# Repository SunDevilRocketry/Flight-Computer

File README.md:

<h1>Flight Computer</h1>

<p><b>Current PCB Revision:</b> 2.0</p>
<p><b>PCB Part Number:</b> A0002</p>

<p>The Avionics team aims to produce a general purpose flight computer 
 for use in high powered rocketry projects that require an embedded processor
specialized for state estimation and control system implementation. The Avionics
flight computer PCB uses an ARM Microcontroller with embedded control and 
navigation sensors to provide a computationally capable embedded protoyping 
platform for high powered rocketry projects with minimal wiring and a small
 form factor.</p>

<b>Working Directory Structure:</b>
 
 <p>
doc: documentation
    
src: source design files, e.g. schematic and board files
 
lib: libraries for schematic symbols and footprints
 
production: files needed for pcb fabrication, e.g. gerbers, profile, drill fi    le
 
 sim: simulation files 
  
 cad: 3d models
   
 img: images of circuit/footprints for github display 
 </p>

<h2>3D Model: </h2>

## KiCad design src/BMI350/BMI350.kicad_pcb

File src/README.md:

<h1>Source Design Files</h1>

Folder for all PCB design files, including project, schematic, and PCB layout 
files

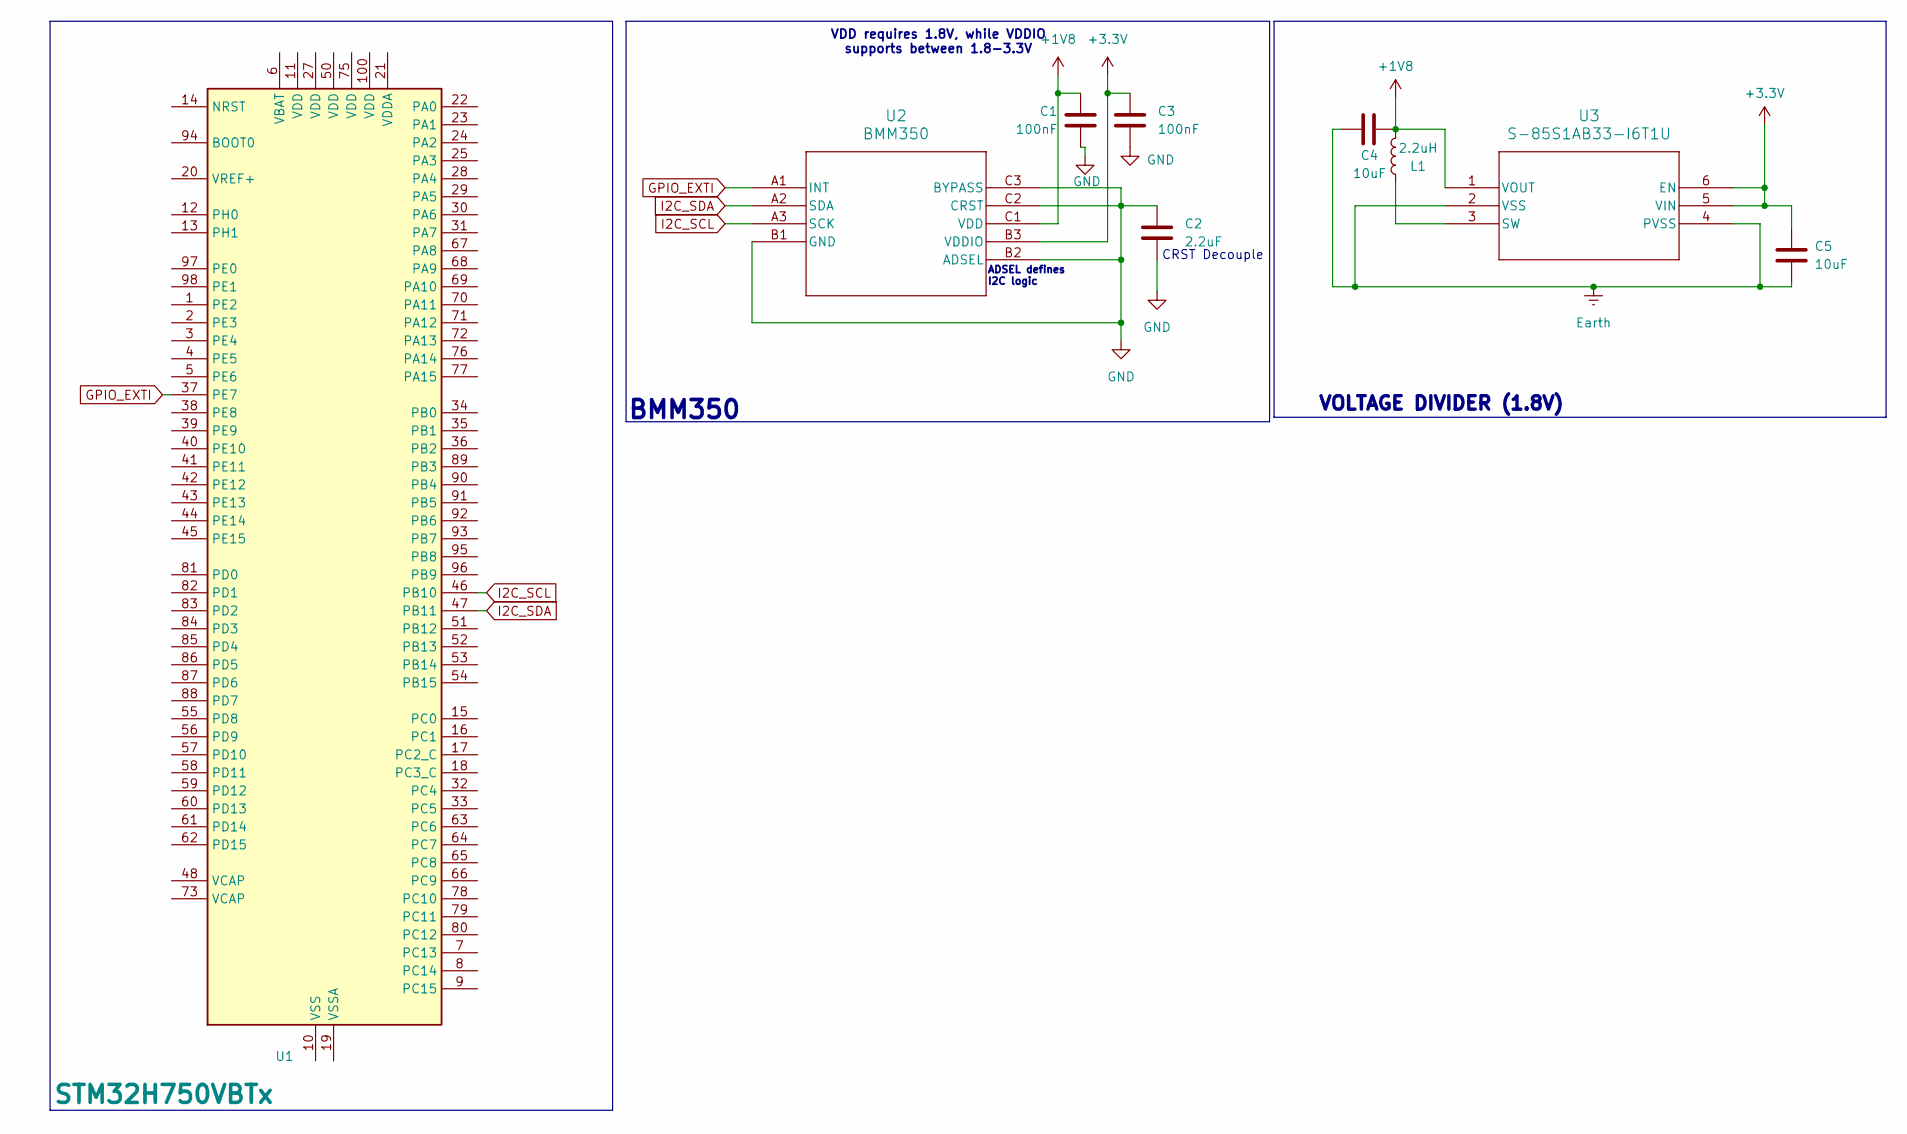
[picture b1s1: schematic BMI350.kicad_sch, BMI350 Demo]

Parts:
C1, C3: 100nF; C_0201_0603Metric
C2: 2.2uF; C_0201_0603Metric
C4, C5: 10uF; C_0201_0603Metric
L1: 2.2uH; L_0201_0603Metric
U1: STM32H750VBTx; LQFP-100_14x14mm_P0.5mm
U2: BMM350; BGA9_BMM350_BOS
U3: S-85S1AB33-I6T1U; SNT-6A-A-PKG_PG006-A-P-SD-2.1_ABL

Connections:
+1V8: C1.2, C4.2, L1.2, U2.C1 (VDD), U3.1 (VOUT)
+3.3V: C3.1, C5.1, U2.B3 (VDDIO), U3.5 (VIN), U3.6 (EN)
Earth: C4.1, C5.2, U3.2 (VSS), U3.4 (PVSS)
GND: C1.1, C2.1, C2.2, C3.2, U2.B1 (GND), U2.B2 (ADSEL), U2.C2 (CRST), U2.C3 (BYPASS)
GPIO_EXTI: U1.37 (PE7), U2.A1 (INT)
I2C_SCL: U1.46 (PB10), U2.A3 (SCK)
I2C_SDA: U1.47 (PB11), U2.A2 (SDA)
unnamed: U1.10 (VSS), U1.26 (VSS), U1.49 (VSS), U1.74 (VSS), U1.99 (VSS)
unnamed: L1.1, U3.3 (SW)

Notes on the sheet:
VOLTAGE DIVIDER (1.8V)
CRST Decouple
BMM350
VDD requires 1.8V, while VDDIO supports between 1.8-3.3V
ADSEL defines I2C logic

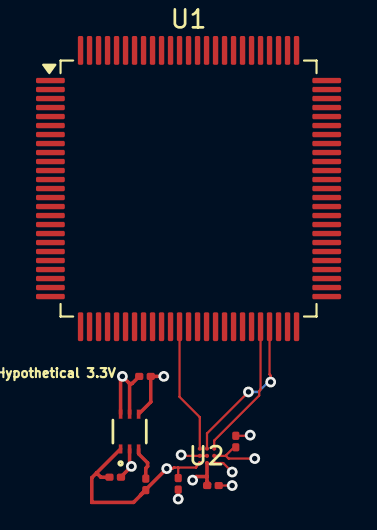
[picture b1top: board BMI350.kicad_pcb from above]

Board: 2 copper layers, 9 parts (0 on the bottom side), 9 nets.

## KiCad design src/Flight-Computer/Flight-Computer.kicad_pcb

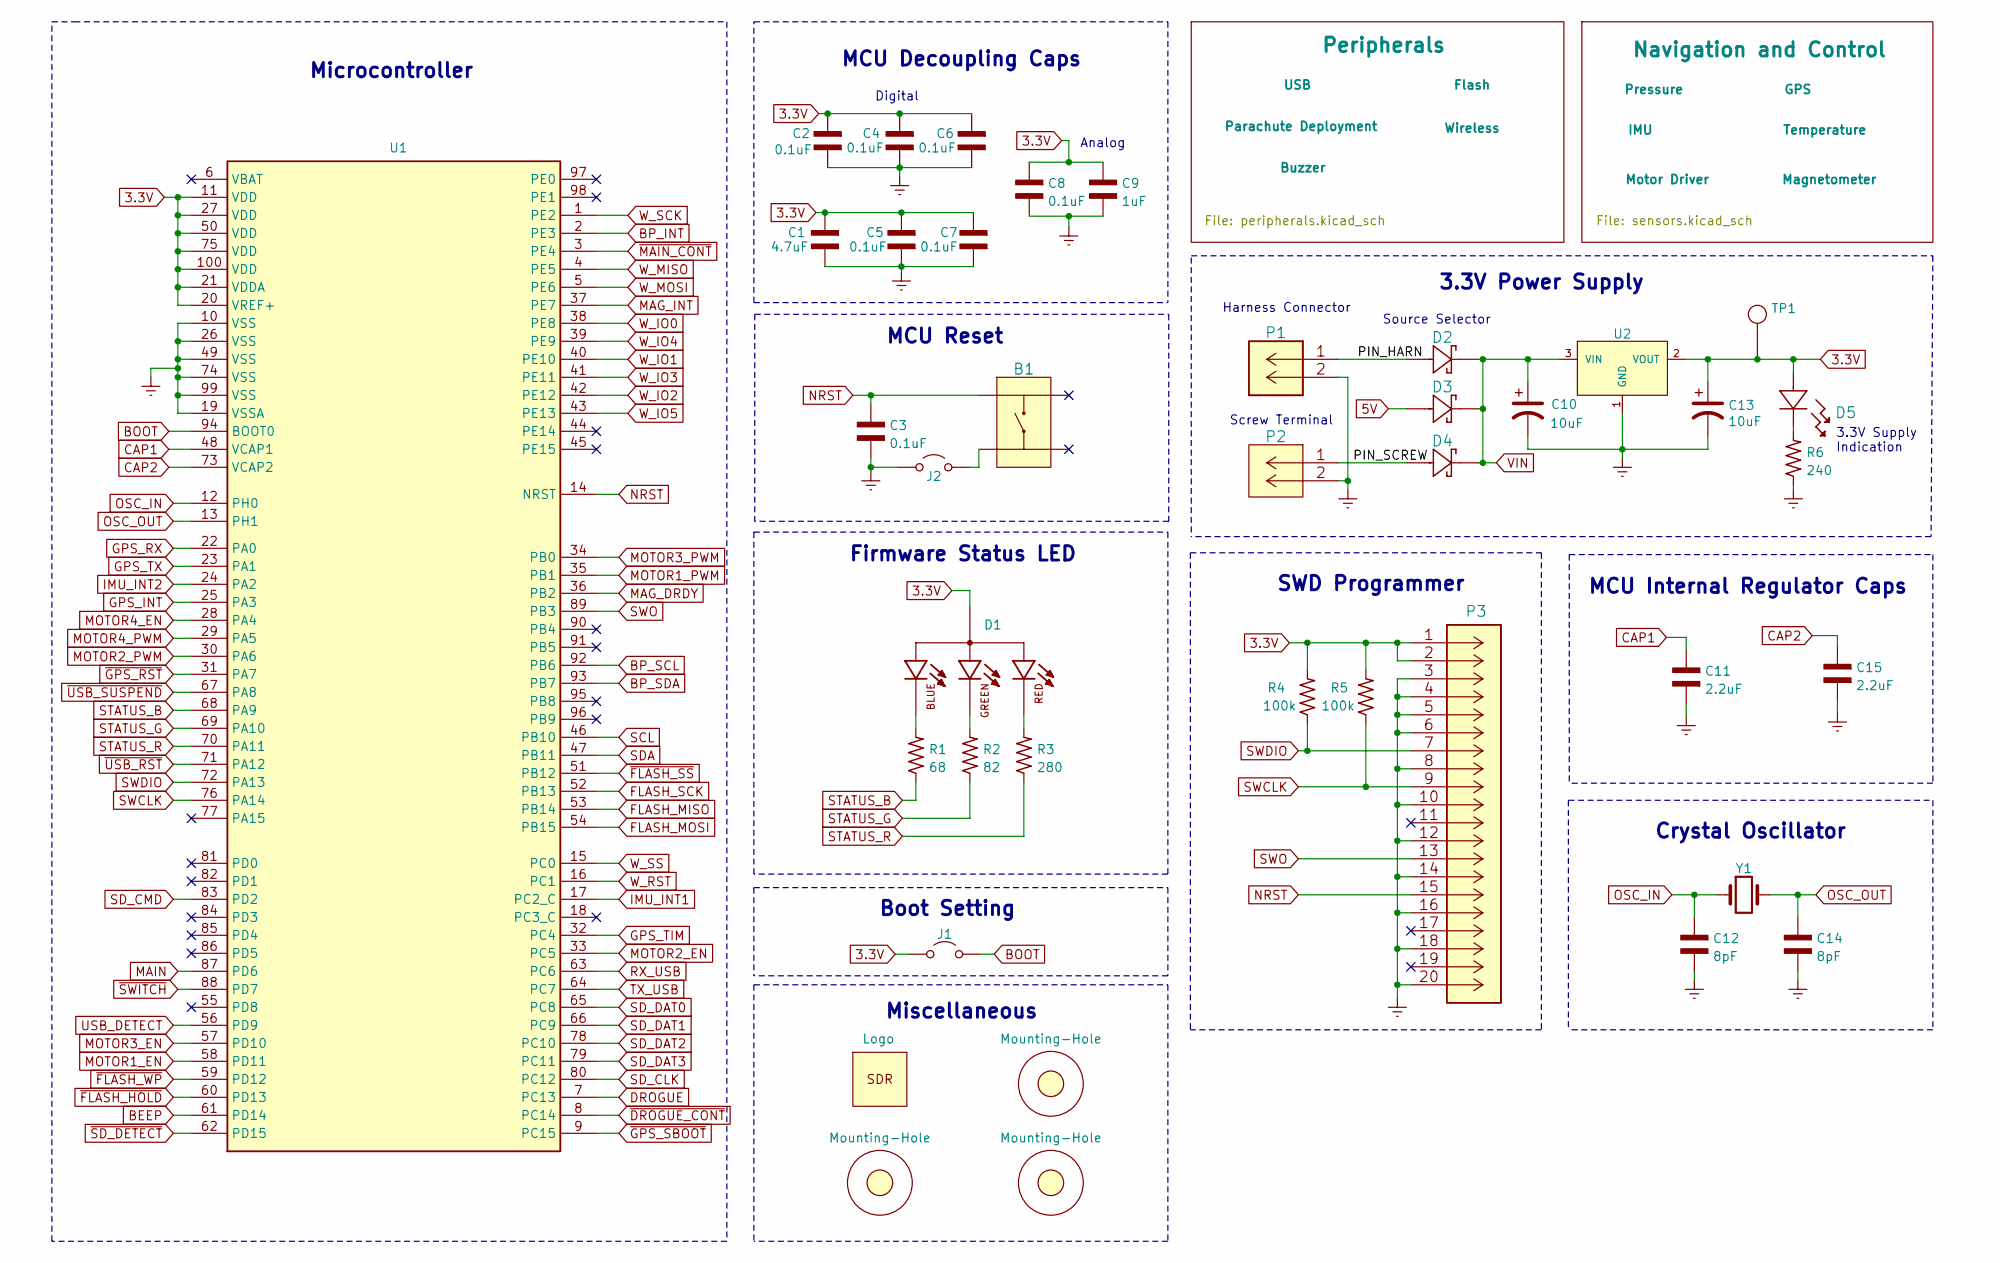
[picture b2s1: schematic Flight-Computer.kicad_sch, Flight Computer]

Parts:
B1: PTS647SM38SMTR2LFS
C1: 4.7uF; CAP_0603
C2, C3, C4, C5, C6, C7: 0.1uF; CAP_0603
C8: 0.1uF; C_0201_0603Metric
C9: 1uF; C_0201_0603Metric
C10, C13: 10uF; T491A106K010AT
C11, C15: 2.2uF; CAP_0603
C12, C14: 8pF; CAP_0603
D1: CLMVC-FKA-CL1D1L71BB7C3C3
D2, D3, D4: SM5819PL-TP
D5: SML-LX1206GC-TR
H1, H2, H3: Mounting-Hole; MountingHole_3mm
J1, J2: Jumper_NO; Jumper-NO
LOGO1: Logo
P1: 647676-2
P2: 1546551-2
P3: 3220-20-0200-00
R1: 68; RES_0603
R2: 82; RES_0603
R3: 280; RES_0603
R4, R5: 100k; RES_0603
R6: 240; RES_0603
TP1: TP
U1: STM32H750VBTx; STM32H750VBT6
U2: LMS8117AMP-3.3_NOPB; LMS8117AMP-3.3NOPB
Y1: ECS-240-18-33-JGN-TR

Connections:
3.3V: C1.1, C2.1, C4.1, C5.1, C6.1, C7.1, C8.1, C9.1, C13.1, D1.1, D5.2, J1.1 (A), P3.1, P3.2, R4.2, R5.2, TP1.1, U1.11 (VDD), U1.20 (VREF+), U1.21 (VDDA), U1.27 (VDD), U1.50 (VDD), U1.75 (VDD), U1.100 (VDD), U2.2 (VOUT); also elsewhere on the board
5V: D3.2; also elsewhere on the board
/PIN_HARN: D2.2, P1.1
/PIN_SCREW: D4.2, P2.1 (5)
BEEP: U1.61 (PD14); also elsewhere on the board
BOOT: J1.2 (B), U1.94 (BOOT0)
BP_INT: U1.2 (PE3); also elsewhere on the board
BP_SCL: U1.92 (PB6); also elsewhere on the board
BP_SDA: U1.93 (PB7); also elsewhere on the board
CAP1: C11.1, U1.48 (VCAP1)
CAP2: C15.1, U1.73 (VCAP2)
DROGUE: U1.7 (PC13); also elsewhere on the board
Earth: C1.2, C2.2, C3.2, C4.2, C5.2, C6.2, C7.2, C8.2, C9.2, C10.2, C11.2, C12.2, C13.2, C14.2, C15.2, J2.1 (A), P1.2, P2.2 (6), P3.3, P3.4, P3.5, P3.6, P3.8, P3.10, P3.12, P3.14, P3.16, P3.18, P3.20, R6.1, U1.10 (VSS), U1.19 (VSSA), U1.26 (VSS), U1.49 (VSS), U1.74 (VSS), U1.99 (VSS), U2.1 (GND); also elsewhere on the board
FLASH_MISO: U1.53 (PB14); also elsewhere on the board
FLASH_MOSI: U1.54 (PB15); also elsewhere on the board
FLASH_SCK: U1.52 (PB13); also elsewhere on the board
GPS_INT: U1.25 (PA3); also elsewhere on the board
GPS_RX: U1.22 (PA0); also elsewhere on the board
GPS_TIM: U1.32 (PC4); also elsewhere on the board
GPS_TX: U1.23 (PA1); also elsewhere on the board
IMU_INT1: U1.17 (PC2_C); also elsewhere on the board
IMU_INT2: U1.24 (PA2); also elsewhere on the board
MAG_DRDY: U1.36 (PB2)
MAG_INT: U1.37 (PE7); also elsewhere on the board
MAIN: U1.87 (PD6); also elsewhere on the board
MOTOR1_EN: U1.58 (PD11); also elsewhere on the board
MOTOR1_PWM: U1.35 (PB1); also elsewhere on the board
MOTOR2_EN: U1.33 (PC5); also elsewhere on the board
MOTOR2_PWM: U1.30 (PA6); also elsewhere on the board
MOTOR3_EN: U1.57 (PD10); also elsewhere on the board
MOTOR3_PWM: U1.34 (PB0); also elsewhere on the board
MOTOR4_EN: U1.28 (PA4); also elsewhere on the board
MOTOR4_PWM: U1.29 (PA5); also elsewhere on the board
NRST: B1.3, C3.1, P3.15, U1.14 (NRST)
unnamed: D1.2, R1.2
unnamed: D1.3, R2.2
unnamed: D1.4, R3.2
unnamed: D5.1, R6.2
unnamed: B1.1, J2.2 (B)
OSC_IN: C12.1, U1.12 (PH0), Y1.1
OSC_OUT: C14.1, U1.13 (PH1), Y1.3
RX_USB: U1.63 (PC6); also elsewhere on the board
SCL: U1.46 (PB10); also elsewhere on the board
SDA: U1.47 (PB11); also elsewhere on the board
SD_CLK: U1.80 (PC12); also elsewhere on the board
SD_CMD: U1.83 (PD2); also elsewhere on the board
SD_DAT0: U1.65 (PC8); also elsewhere on the board
SD_DAT1: U1.66 (PC9); also elsewhere on the board
SD_DAT2: U1.78 (PC10); also elsewhere on the board
SD_DAT3: U1.79 (PC11); also elsewhere on the board
STATUS_B: R1.1, U1.68 (PA9)
STATUS_G: R2.1, U1.69 (PA10)
STATUS_R: R3.1, U1.70 (PA11)
SWCLK: P3.9, R5.1, U1.76 (PA14)
SWDIO: P3.7, R4.1, U1.72 (PA13)
SWO: P3.13, U1.89 (PB3)
TX_USB: U1.64 (PC7); also elsewhere on the board
USB_DETECT: U1.56 (PD9); also elsewhere on the board
VIN: C10.1, D2.1, D3.1, D4.1, U2.3 (VIN); also elsewhere on the board
W_IO0: U1.38 (PE8); also elsewhere on the board
W_IO1: U1.40 (PE10); also elsewhere on the board
W_IO2: U1.42 (PE12); also elsewhere on the board
W_IO3: U1.41 (PE11); also elsewhere on the board
W_IO4: U1.39 (PE9); also elsewhere on the board
W_IO5: U1.43 (PE13); also elsewhere on the board
W_MISO: U1.4 (PE5); also elsewhere on the board
W_MOSI: U1.5 (PE6); also elsewhere on the board
W_RST: U1.16 (PC1); also elsewhere on the board
W_SCK: U1.1 (PE2); also elsewhere on the board
W_SS: U1.15 (PC0); also elsewhere on the board
~DROGUE_CONT: U1.8 (PC14); also elsewhere on the board
~FLASH_HOLD: U1.60 (PD13); also elsewhere on the board
~FLASH_SS: U1.51 (PB12); also elsewhere on the board
~FLASH_WP: U1.59 (PD12); also elsewhere on the board
~GPS_RST: U1.31 (PA7); also elsewhere on the board
~GPS_SBOOT: U1.9 (PC15); also elsewhere on the board
~MAIN_CONT: U1.3 (PE4); also elsewhere on the board
~SD_DETECT: U1.62 (PD15); also elsewhere on the board
~SWITCH: U1.88 (PD7); also elsewhere on the board
~USB_RST: U1.71 (PA12); also elsewhere on the board
~USB_SUSPEND: U1.67 (PA8); also elsewhere on the board

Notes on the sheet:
Crystal Oscillator
3.3V Power Supply
MCU Internal Regulator Caps
MCU Reset
Firmware Status LED
3.3V Supply Indication
Source Selector
MCU Decoupling Caps
Boot Setting
Miscellaneous
Analog
Screw Terminal
Microcontroller
Harness Connector
Digital
SWD Programmer

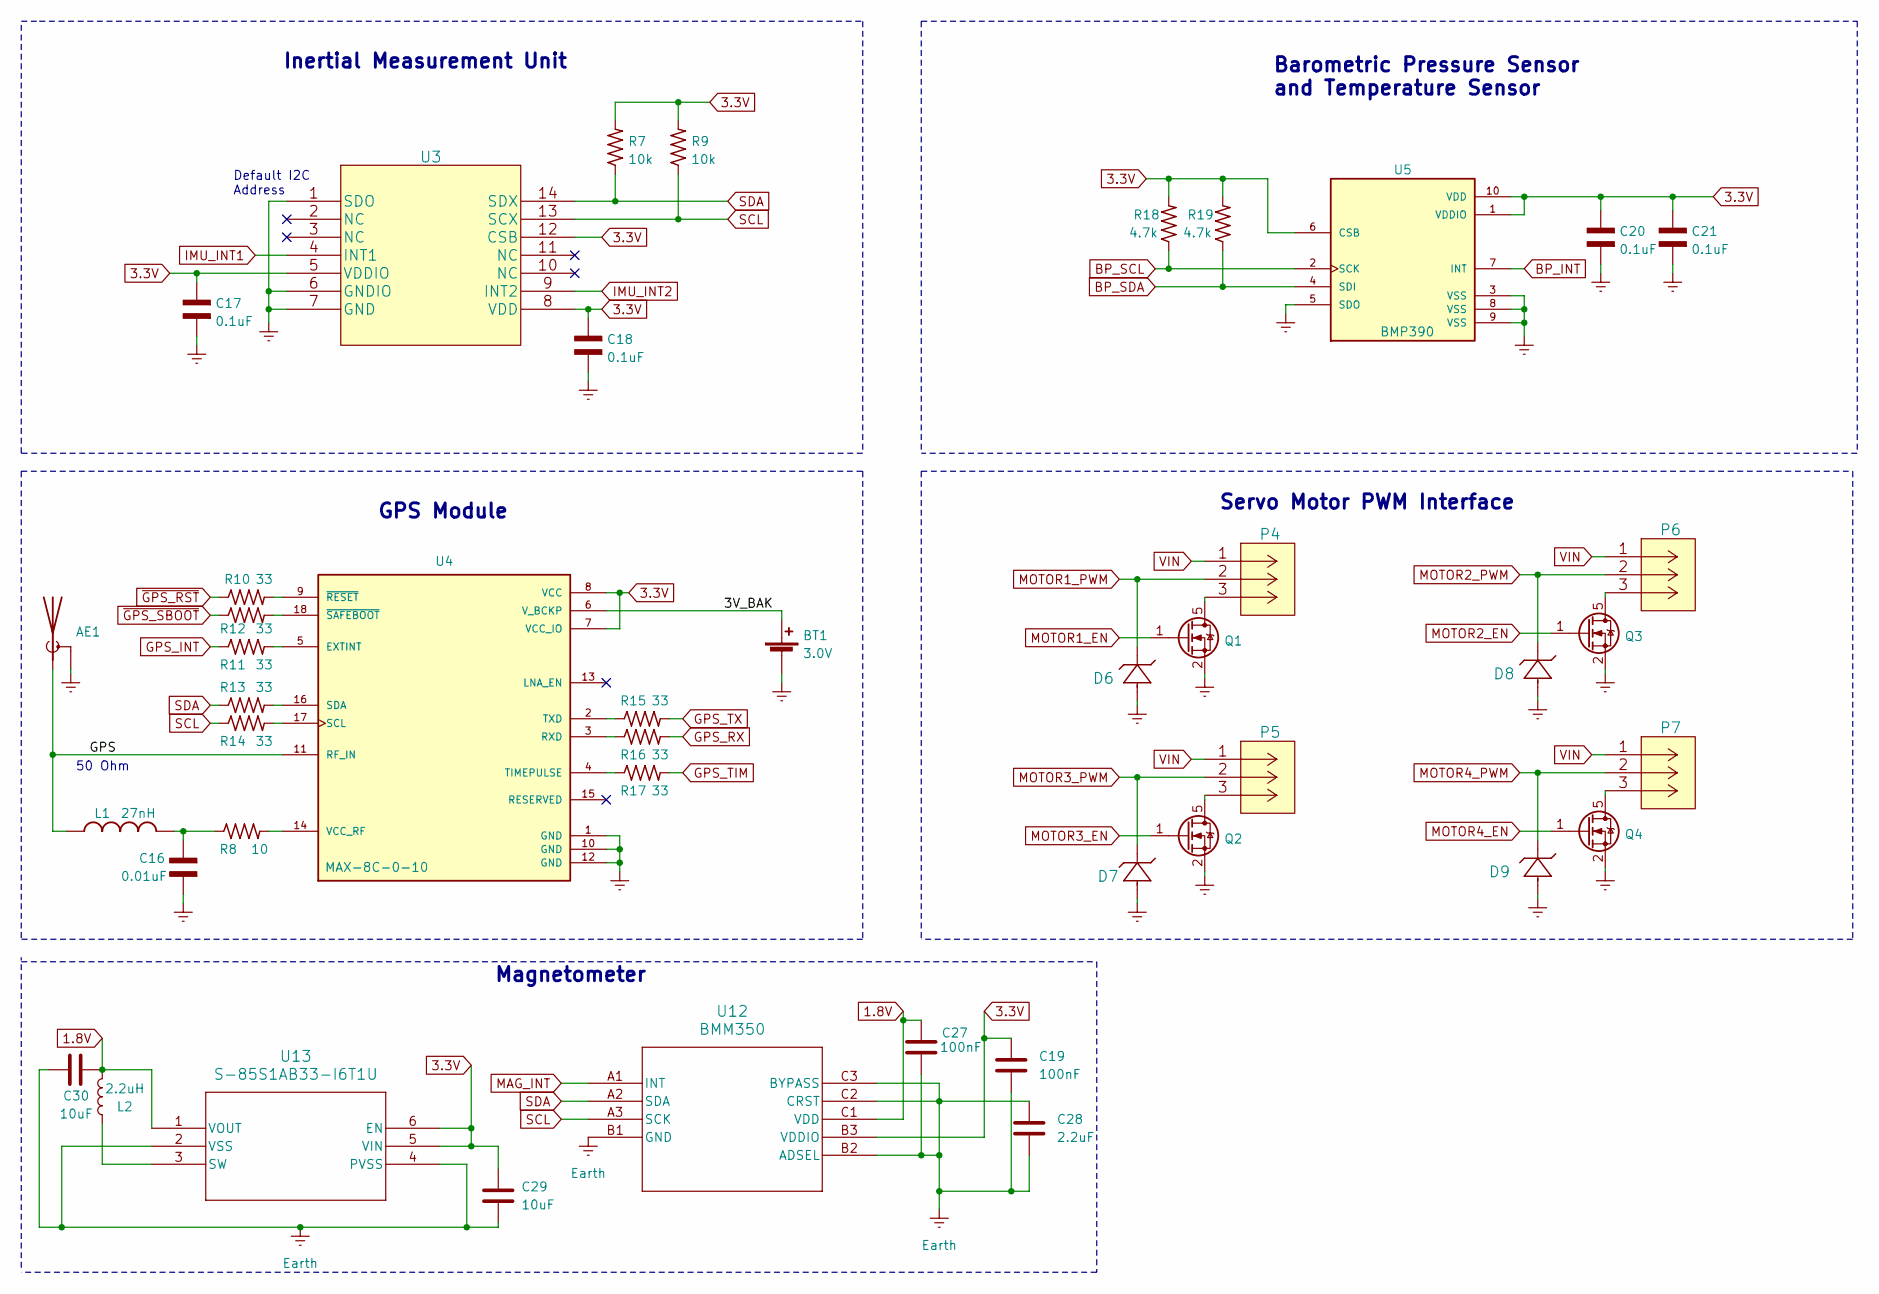
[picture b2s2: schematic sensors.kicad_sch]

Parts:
AE1: 0734120110; 73412-0110
BT1: MS614SE-FL28E; MS621FE-FL11E; Voltage 3.0V
C16: 0.01uF; CAP_0603
C17, C20, C21: 0.1uF; CAP_0603
C18: 0.1uF; C_0201_0603Metric
C19, C27: 100nF; C_0201_0603Metric
C28: 2.2uF; C_0201_0603Metric
C29, C30: 10uF; C_0201_0603Metric
D6, D7, D8, D9: MM3Z3V3B
L1: 27nH; L-07C27NJV6T
L2: 2.2uH; L_0201_0603Metric
P4, P5, P6, P7: 440054-3
Q1, Q2, Q3, Q4: QS5U17TR
R7, R9: 10k; RES_0603
R8: 10; RES_0603
R10, R11, R12, R13, R14, R15, R16, R17: 33; RES_0603
R18, R19: 4.7k; RES_0603
U3: BMI323
U4: MAX-8C-0-10; MAX-8C-0
U5: BMP390
U12: BMM350; BGA9_BMM350_BOS
U13: S-85S1AB33-I6T1U; SNT-6A-A-PKG_PG006-A-P-SD-2.1_ABL

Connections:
1.8V: C27.1, C30.2, L2.2, U12.C1 (VDD), U13.1 (VOUT)
3.3V: C17.1, C18.1, C19.1, C20.1, C21.1, C29.1, R7.2, R9.2, R18.2, R19.2, U3.5 (VDDIO), U3.8 (VDD), U3.12 (CSB), U4.7 (VCC_IO), U4.8 (VCC), U5.1 (VDDIO), U5.6 (CSB), U5.10 (VDD), U12.B3 (VDDIO), U13.5 (VIN), U13.6 (EN); also elsewhere on the board
/Navigation and Control/3V_BAK: BT1.1 (+), U4.6 (V_BCKP)
/Navigation and Control/GPS: AE1.1 (A), L1.1, U4.11 (RF_IN)
BP_INT: U5.7 (INT); also elsewhere on the board
BP_SCL: R18.1, U5.2 (SCK); also elsewhere on the board
BP_SDA: R19.1, U5.4 (SDI); also elsewhere on the board
Earth: AE1.2 (Shield), BT1.2 (-), C16.2, C17.2, C18.2, C19.2, C20.2, C21.2, C27.2, C28.1, C28.2, C29.2, C30.1, D6.2, D7.2, D8.2, D9.2, Q1.2 (S), Q2.2 (S), Q3.2 (S), Q4.2 (S), U3.1 (SDO), U3.6 (GNDIO), U3.7 (GND), U4.1 (GND), U4.10 (GND), U4.12 (GND), U5.3 (VSS), U5.5 (SDO), U5.8 (VSS), U5.9 (VSS), U12.B1 (GND), U12.B2 (ADSEL), U12.C2 (CRST), U12.C3 (BYPASS), U13.2 (VSS), U13.4 (PVSS); also elsewhere on the board
GPS_INT: R12.1; also elsewhere on the board
GPS_RX: R16.2; also elsewhere on the board
GPS_TIM: R17.2; also elsewhere on the board
GPS_TX: R15.2; also elsewhere on the board
IMU_INT1: U3.4 (INT1); also elsewhere on the board
IMU_INT2: U3.9 (INT2); also elsewhere on the board
MAG_INT: U12.A1 (INT); also elsewhere on the board
MOTOR1_EN: Q1.1 (G); also elsewhere on the board
MOTOR1_PWM: D6.1, P4.2 (GND); also elsewhere on the board
MOTOR2_EN: Q3.1 (G); also elsewhere on the board
MOTOR2_PWM: D8.1, P6.2 (GND); also elsewhere on the board
MOTOR3_EN: Q2.1 (G); also elsewhere on the board
MOTOR3_PWM: D7.1, P5.2 (GND); also elsewhere on the board
MOTOR4_EN: Q4.1 (G); also elsewhere on the board
MOTOR4_PWM: D9.1, P7.2 (GND); also elsewhere on the board
unnamed: C16.1, L1.2, R8.1
unnamed: P4.3, Q1.5 (D)
unnamed: P5.3, Q2.5 (D)
unnamed: P6.3, Q3.5 (D)
unnamed: P7.3, Q4.5 (D)
unnamed: R12.2, U4.5 (EXTINT)
unnamed: R16.1, U4.3 (RXD)
unnamed: R14.2, U4.17 (SCL)
unnamed: R13.2, U4.16 (SDA)
unnamed: R17.1, U4.4 (TIMEPULSE)
unnamed: R15.1, U4.2 (TXD)
unnamed: R8.2, U4.14 (VCC_RF)
unnamed: R10.2, U4.9 (~RESET)
unnamed: R11.2, U4.18 (~SAFEBOOT)
unnamed: L2.1, U13.3 (SW)
SCL: R9.1, R14.1, U3.13 (SCX), U12.A3 (SCK); also elsewhere on the board
SDA: R7.1, R13.1, U3.14 (SDX), U12.A2 (SDA); also elsewhere on the board
VIN: P4.1 (+12V), P5.1 (+12V), P6.1 (+12V), P7.1 (+12V); also elsewhere on the board
~GPS_RST: R10.1; also elsewhere on the board
~GPS_SBOOT: R11.1; also elsewhere on the board

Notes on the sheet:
Default I2C Address
Servo Motor PWM Interface
50 Ohm
Magnetometer
GPS Module
Barometric Pressure Sensor and Temperature Sensor
Inertial Measurement Unit

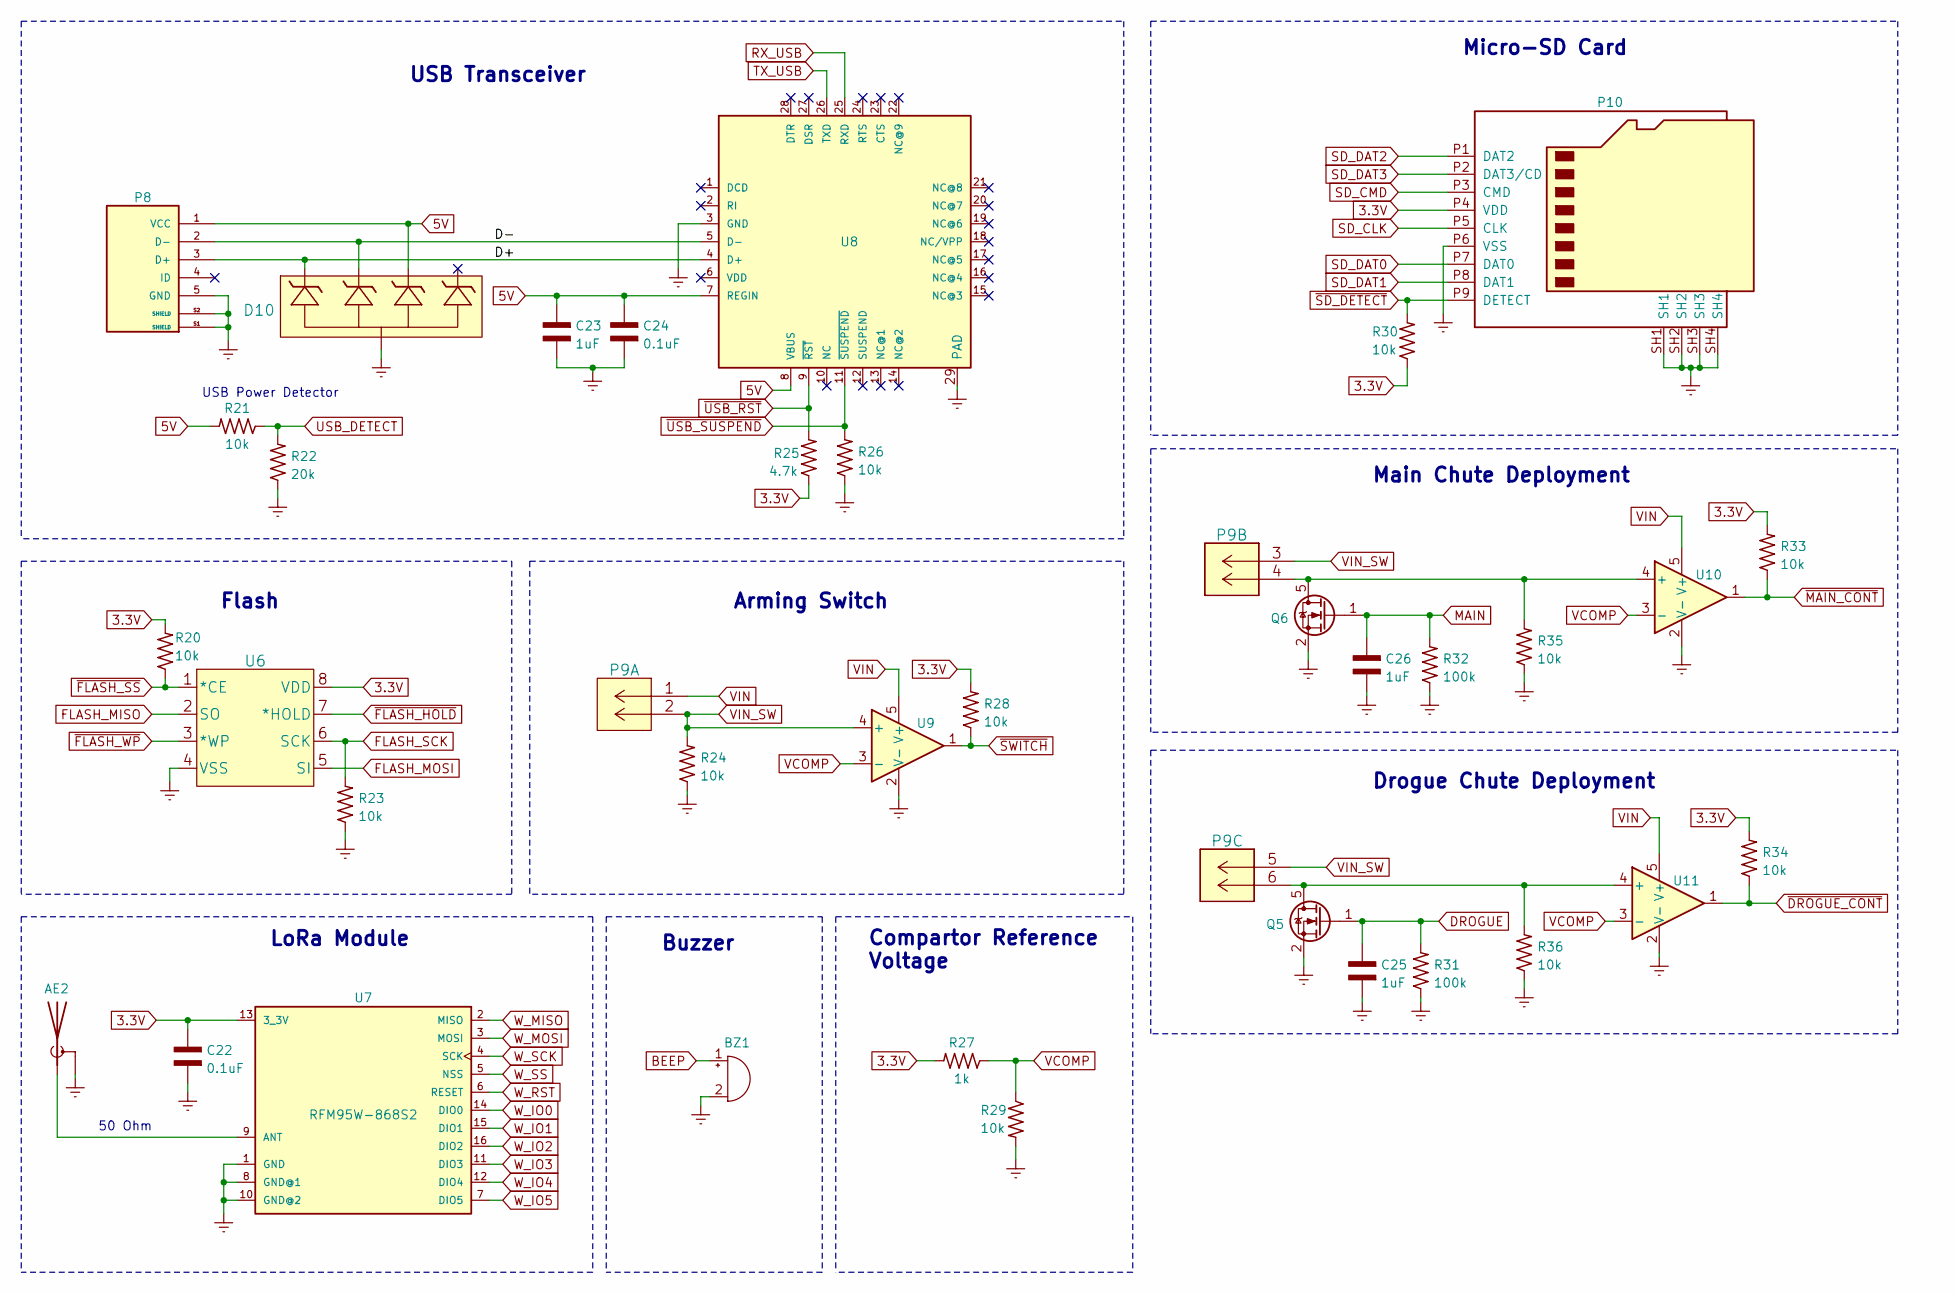
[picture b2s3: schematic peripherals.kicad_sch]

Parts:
AE2: 142-0701-851
BZ1: AT-1438-TWT-R
C22: 0.1uF; C_0201_0603Metric
C23, C25, C26: 1uF; CAP_0603
C24: 0.1uF; CAP_0603
D10: SP0504BAHTG
P8: USB; 10118194-0001LF
P9: 1984659
P10: Micro_SD_Card; MEM2075-00-140-01-A
Q5, Q6: QS5U17TR
R20, R21, R23, R24, R26, R28, R29, R30, R33, R34, R35, R36: 10k; RES_0603
R22: 20k; RES_0603
R25: 4.7k; RES_0603
R27: 1k; RES_0603
R31, R32: 100k; RES_0603
U6: SST25VF040B-50-4I-S2AE-T
U7: RFM95W-868S2; RFM95
U8: CP2102-GMR(QFN28); CP2012-GMR; MPN CP2102-GMR
U9, U10, U11: TS391IYLT

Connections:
3.3V: C22.1, P10.P4 (VDD), R20.2, R25.1, R27.2, R28.2, R30.1, R33.2, R34.2, U6.8 (VDD), U7.13 (3_3V); also elsewhere on the board
5V: C23.1, C24.1, D10.4, P8.1 (VCC), R21.2, U8.7 (REGIN), U8.8 (VBUS); also elsewhere on the board
/Peripherals/D+: D10.1, P8.3 (D+), U8.4 (D+)
/Peripherals/D-: D10.3, P8.2 (D-), U8.5 (D-)
BEEP: BZ1.1 (-); also elsewhere on the board
DROGUE: C25.1, Q5.1 (G), R31.2; also elsewhere on the board
Earth: AE2.2 (Shield), BZ1.2 (+), C22.2, C23.2, C24.2, C25.2, C26.2, D10.2, P8.5 (GND), P8.S1 (SHIELD), P8.S2 (SHIELD), P10.P6 (VSS), P10.SH1, P10.SH2, P10.SH3, P10.SH4, Q5.2 (S), Q6.2 (S), R22.1, R23.1, R24.1, R26.1, R29.2, R31.1, R32.1, R35.1, R36.1, U6.4 (VSS), U7.1 (GND), U7.8 (GND@1), U7.10 (GND@2), U8.3 (GND), U8.29 (PAD), U9.2 (V-), U10.2 (V-), U11.2 (V-); also elsewhere on the board
FLASH_MISO: U6.2 (SO); also elsewhere on the board
FLASH_MOSI: U6.5 (SI); also elsewhere on the board
FLASH_SCK: R23.2, U6.6 (SCK); also elsewhere on the board
MAIN: C26.1, Q6.1 (G), R32.2; also elsewhere on the board
unnamed: AE2.1 (A), U7.9 (ANT)
unnamed: P9.4 (6), Q6.5 (D), R35.2, U10.4 (+)
unnamed: P9.6, Q5.5 (D), R36.2, U11.4 (+)
RX_USB: U8.25 (RXD); also elsewhere on the board
SD_CLK: P10.P5 (CLK); also elsewhere on the board
SD_CMD: P10.P3 (CMD); also elsewhere on the board
SD_DAT0: P10.P7 (DAT0); also elsewhere on the board
SD_DAT1: P10.P8 (DAT1); also elsewhere on the board
SD_DAT2: P10.P1 (DAT2); also elsewhere on the board
SD_DAT3: P10.P2 (DAT3/CD); also elsewhere on the board
TX_USB: U8.26 (TXD); also elsewhere on the board
USB_DETECT: R21.1, R22.2; also elsewhere on the board
VCOMP: R27.1, R29.1, U9.3 (-), U10.3 (-), U11.3 (-)
VIN: P9.1 (5), U9.5 (V+), U10.5 (V+), U11.5 (V+); also elsewhere on the board
VIN_SW: P9.2 (6), P9.3 (5), P9.5, R24.2, U9.4 (+)
W_IO0: U7.14 (DIO0); also elsewhere on the board
W_IO1: U7.15 (DIO1); also elsewhere on the board
W_IO2: U7.16 (DIO2); also elsewhere on the board
W_IO3: U7.11 (DIO3); also elsewhere on the board
W_IO4: U7.12 (DIO4); also elsewhere on the board
W_IO5: U7.7 (DIO5); also elsewhere on the board
W_MISO: U7.2 (MISO); also elsewhere on the board
W_MOSI: U7.3 (MOSI); also elsewhere on the board
W_RST: U7.6 (RESET); also elsewhere on the board
W_SCK: U7.4 (SCK); also elsewhere on the board
W_SS: U7.5 (NSS); also elsewhere on the board
~DROGUE_CONT: R34.1, U11.1; also elsewhere on the board
~FLASH_HOLD: U6.7 (*HOLD); also elsewhere on the board
~FLASH_SS: R20.1, U6.1 (*CE); also elsewhere on the board
~FLASH_WP: U6.3 (*WP); also elsewhere on the board
~MAIN_CONT: R33.1, U10.1; also elsewhere on the board
~SD_DETECT: P10.P9 (DETECT), R30.2; also elsewhere on the board
~SWITCH: R28.1, U9.1; also elsewhere on the board
~USB_RST: R25.2, U8.9 (~RST); also elsewhere on the board
~USB_SUSPEND: R26.2, U8.11 (~SUSPEND); also elsewhere on the board

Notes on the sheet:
Micro-SD Card
Compartor Reference Voltage
USB Power Detector
Arming Switch
50 Ohm
Drogue Chute Deployment
Buzzer
Flash
USB Transceiver
Main Chute Deployment
LoRa Module

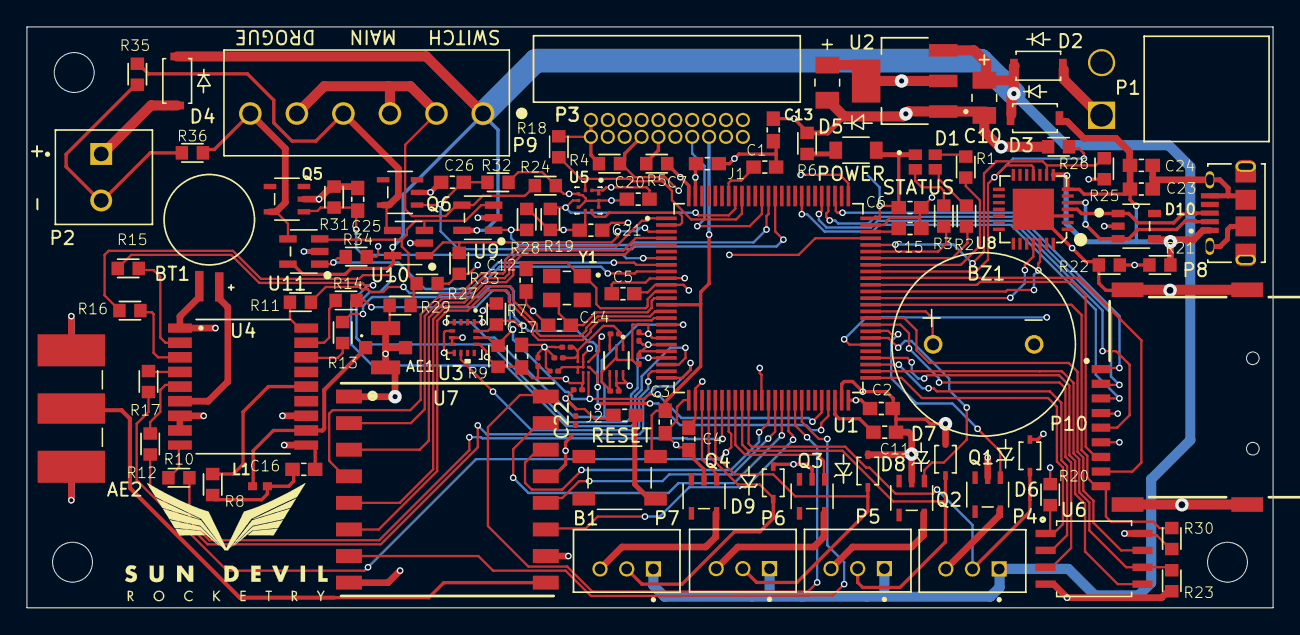
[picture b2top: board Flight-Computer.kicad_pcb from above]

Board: 4 copper layers, 93.7 x 43.7 mm, 120 parts (1 on the bottom side), 105 nets.

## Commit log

2021-07-14 Copied PCB file structure
2021-07-14 Added description to readme
2021-07-14 Started lib files
2021-07-20 Added caps and resistors to lib files
2021-07-20 Added programming connector to lib files
2021-07-20 added linear regulator parts to lib files
2021-09-12 Backup file
2021-09-12 Test
2021-09-23 Copied files from L0002 directory
2021-09-23 Removed demo git commit from README
2022-05-22 deleted engine controller symbols from library
2022-05-22 added 3D files to base lib files
2022-05-22 remove unecessary symbols from lib files
2022-05-22 added green LED to lib files
2022-05-22 added tantalum capacitor to lib files
2022-05-22 added power mosfet to lib files
2022-05-22 added programmer connector to lib files
2022-05-22 edited title of readme
2022-05-22 added ESD chip to lib files
2022-05-22 added screw terminals for ematches
2022-05-22 added rgb LED to lib files
2022-05-22 added crystal to lib files
2022-05-22 added power screw terminal to lib files
2022-05-22 cleaned up mcu schematic
2022-05-22 added logo and mounting holes to lib files
2022-05-22 implemented rgb led in schematic
2022-05-22 added logo and mounting holes to schematic
2022-05-22 implemented crystal oscillator in schematic
2022-05-22 implemented mcu decoupling and regulator caps in schematic
2022-05-22 deleted connector schematic sheet
2022-05-22 added second sheet for peripheral functionality
2022-05-22 added main power connector to lib files
2022-05-22 added schottky diode to lib files
2022-05-22 implemented 3.3V regulator in schematic
2022-05-22 plotted schematic to pdf
2022-05-22 added uart to usb bridge to lib files
2022-05-22 added usb connector to lib files
2022-05-22 implemented usb transceiver in schematic
2022-05-22 updated schematic pdf with usb transceiver
2022-05-23 implemented flash in schematic
2022-05-23 added comparator to lib files
2022-05-23 implemented parachute deployment circuitry in schematic
2022-05-23 added usb data traces to mcu in schematic
2022-05-23 added IMU to lib files
2022-05-23 added buzzer to lib files
2022-05-28 added sensors sheet
2022-05-28 implemented IMU in schematic
2022-05-28 adjusted imu resistor labels
2022-05-28 added imu i2c signals to mcu in schematic
2022-05-28 added parachute deployment label to peripherals sheet
2022-05-28 added gps module to lib files
2022-05-28 added more labels to subsheets
2022-05-28 added LoRa module to lib files
2022-05-28 added pressure sensor to lib files
2022-05-29 added gps antenna jack to lib files
2022-05-29 added backup battery to lib files
2022-05-29 implemented gps module for passive antenna design
2022-05-30 implemented buzzer in schematic
2022-05-30 added RF SMA connector to lib files
2022-05-30 implemented lora module in schematic
2022-05-30 added decoupling capacitor to lora module
2022-05-30 implemented barometric pressure sensor in schematic
2022-05-30 changed name of main schematic sheet
2022-05-30 minor schematic formatting changes
2022-05-30 added motor connectors to lib files
2022-06-01 added zener diode to lib files
2022-06-01 implemented pwm motor interface in schematic
2022-06-01 added inductor to lib files
2022-06-01 added power supply for active gps antenna
2022-06-03 added 3d model for BMP390
2022-06-03 added mcu signals for peripherals
2022-06-03 setup layout design rules
2022-06-04 placed pcb parts on board and defined form factor
2022-06-05 routed main peripheral functionality excluding parachute deployment circuitry
2022-06-06 finished routing
2022-06-06 finished resolving DRC errors
2022-06-06 generated 3D model
2022-06-06 added 3d model images to readme
2022-06-06 fixed typo in readme
2022-06-06 minor readme formatting update
2022-06-12 minor updates due to saving files after commiting
2022-09-16 generated gerbers
2022-12-14 final rev1 commit
2022-12-14 added usb detector to schemtaic
2022-12-14 added IMU and magnetometer to lib files
2022-12-14 implemented new imu in schematic
2022-12-15 implemented magnetometer in schematic
2022-12-15 replaced screw terminals with smaller parts
2022-12-15 fixed incorrect LoRa MISO and MOSI connections
2022-12-15 matched footprints to symbols
2022-12-15 started rev 2 routing
2022-12-15 continued rev 2 routing
2022-12-16 continued rev2 routing
2022-12-16 finished rev 2 routing
2022-12-16 resolved rev2 DRC errors
2022-12-16 generated fabrication outputs
2022-12-16 moved POWER label away from board edge
2022-12-16 updated readme to rev 2
2022-12-16 generated Rev2 cad model
2022-12-17 plotted rev2 schematic to pdf
2022-12-17 created initial directory structure
2022-12-17 Revert "created initial directory structure"
    This reverts commit bc7f64fc1d44c54ed575f89b5c5ab804f6935a7a.
2022-12-20 added ignition continuity pull down resistors
2023-01-07 added ignition comparator pull down resistors
2025-01-27 BMM350
    Schematic and Routing for BMM350
2025-01-28 Wrong name
    fixed name of project
2025-02-05 Voltage Divider
    Added voltage divider for BMM350 1.8V power supply
2025-02-05 BMM forgot
    Forgot to save files before pushing
2025-02-05 Voltage Divider
    Fixed voltage divider outputs
2025-02-06 PCB Part 1
    Changed first part of flight computer to BMM 350 schematic
2025-02-07 Buck Converter
    Redid BM350 breakout schematic with 3.3-1.8 buck converter instead of voltage divider
2025-02-08 S-85S1A
    Added S-85S1A to flight computer schematic
2025-02-18 quick fix
    Fixed BMM350 decoupling capacitor issue

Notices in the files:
parts and their libraries:
Copyright 2021 Accelerated Designs. All rights reserved.
